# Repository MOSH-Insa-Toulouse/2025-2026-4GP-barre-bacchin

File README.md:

# Partie I : Contexte 

Le but de ce projet est de réaliser un capteur de flexion lowtech à base de crayon à papier et d'une feuille de papier.  
L'origine de ce projet vient d'un article publié en 2014 dans Nature par _Lin, CW, Zhao, Z., Kim, J. et al._ nommé "**Pencil Drawn Strain Gauges and Chemiresistors on Paper "**.  
Le capteur est dessiné par dépot de graphite sur une feuille à l'aide d'un crayon de papier. Ce dépot est un système granulaire dont la conductance dépend de la distance inter-grain. Plus la distance inter-grain diminue, plus la conductance augmente. C'est exactement ce qu'il se passe lorsque la feuille est placé en compression. De ce fait, on peut théoriquement déduire l'angle de flexion de la feuille en fonction de la résistance du capteur.  
  
Notre travail consiste a réaliser le capteur, le circuit électronique de lecture et de le tester afin de le comparer à des capteurs commerciaux. 

## Partie I.1 : Liste des Livrables

1. Un shield PCB adapté pour une Arduino UNO permettant de faire la mesure de résistance du capteur graphite, celle du capteur commercial et de connecter un module Bluetooth pour envoyer les résulats sur une application.
2. Une application Android (sous MIT App Inventor) permettant de voir la valeur de la résistance mesuré et la variation relative de résistance.
3. Le code Arduino qui gère la mesure de flexion et le module bluetooth
4. Le protocole de mesure du banc de test
5. La datasheet du capteur graphite

## Partie I.2 : Liste du matériel utilisé

1. Capteur en graphite 
   - Feuille de papier d'épaisseur 0.35mm
   - Différents crayons à papier (B, 3B et 6B)
2. Arduino et modules
   - Carte Arduino UNO + câble USB
   - Module Bluetooth HC-05
   - Flex Sensor + résistance de 47 kΩ
3. Circuit amplificateur
   - Amplificateur opérationnel LTC1050
   - Condensateurs : 2* 100 nF + 1* 1 µF
   - Résistances :  1* 1kΩ + 1* 10kΩ + 2* 100kΩ
   - Potentiomètre digital MCP 41010
4. Matériel pour réaliser le PCB
   - Plaque d'époxy recouverte d'une couche de cuivre et de résine photosensible
   - Matériel de développement : Machine UV + révélateur + perclorure de fer
   - Machine à perforer
   - Fer à souder + étain
   - Pin headers
5. Banc de test
   - Banc de test creux avec différents rayons de courbures connus.

# Partie II : Réalisation théorique

## Partie II.1 : Conception du circuit amplificateur
La résistance du capteur est énorme, de l'ordre du Mega-Ohm, ainsi le courant obtenu en sortie est très faible. Il nous faut donc amplifier le signal afin de l'exploiter.  

Pour ce faire nous avons réaliser un circuit amplificateur transimpédance que nous avons simulé sur LTSpice visible en figure II.1
<p align="center">
  <br>
  <em>Figure II.1 – Schéma LTSpice du capteur et du circuit amplificateur</em>
</p>

Sur le logiciel de simulation, nous avons modélisé l’alimentation de l’Arduino en 5 V, alimentation qui fournit également l’énergie nécessaire au capteur et à l’amplificateur opérationnel (AOP).
Le capteur a ensuite été représenté à l’aide d’un générateur de pulses, ce qui permet de simuler son comportement dynamique.
Afin de reproduire des conditions réelles, une source de bruit a été ajoutée au montage. 

Le circuit amplificateur est constitué de trois filtres passe-bas, chacun ayant un rôle bien précis dans l’élimination des bruits indésirables.

   - Filtre passe-bas 16 Hz (en entrée)

Ce filtre permet de supprimer les bruits parasites provenant de vibrations mécaniques ou de tremblements.

$$ Fc_{1}  = \frac{1}{2\pi * C1 * R1 } = \frac{1}{2\pi * 100n * 100k}  ≃ 16 Hz$$

   - Filtre passe-bas 1.6 Hz (réduction du bruit 50 Hz)

Ce filtre atténue les résidus issus du bruit secteur 50 Hz.

$$ Fc_{2}  = \frac{1}{2\pi * C2 * R4 } = \frac{1}{2\pi * 1µm * 100k}  ≃ 1.6 Hz $$

   - Filtre passe-bas 1.6 kHz (en sortie de l’AOP)

Ce filtre élimine les bruits haute fréquence générés par l’électronique (AOP, câblage, parasites HF).

$$ Fc_{3}  = \frac{1}{2\pi * C3 * R5 } = \frac{1}{2\pi *100n * 1k}  ≃ 1.6 KHz $$

Plusieurs simulations ont été effectuées afin de vérifier :
- L'amplication du signal fourni par le capteur
- La filtration du bruit 

À partir du montage, il est également possible de déterminer la relation mathématique reliant la résistance du capteur à sa tension de sortie : 
<p align="center">
   <br>
  <em> (Eq.1) </em>
</p>

## Partie II.2 : Design du PCB sous KiCad

Une fois la forme du circuit fixé et tous les modules connectés à l'Arduino chosis, nous avons pu concevoir la shield.  
Pour ce faire, nous utilisons le logiciel KiCad. 
Comme tous les composants n'étaient pas présent dans la bibliothèque de composant de KiCad, nous avons dû réalisé les schématiques et les empreintes du flex sensor, du capteur graphite, du module bluetooth et du potentiomètre digital.   
Voilà le schématique complet de notre shield :   

<p align="center">
  <br>
  <em>Figure II.2 – Schématique kicad du projet</em>
</p>

Concernant les empreintes, nous n'allons pas souder les composants onéreux directement. Ainsi pour le flex sensor et le module bluetooth nous avons prévu des pins dans lesquels nous brancherons les modules. Pour l'AOP et le potentiomètre nous allons souder des support DIP8.  
Ainsi notre empreinte ressemble à cela :  
<p align="center">
  <br>
  <em>Figure II.3 – Empreinte du projet</em>
</p>

Enfin la modélisation 3D donne :  

<p align="center">
 <br>
  <em>Figure II.4 – Modélisation 3D du projet</em>
</p>

# Partie III : Fabrication du PCB

Une fois le PCB conçu, vérifié et corrigé sous KiCad, nous pouvons passer à sa fabrication. Pour cela, le circuit est exporté depuis KiCad sous la forme d’un fichier typon, qui servira de base pour la gravure du circuit imprimé.

<p align="center">
 <br>
  <em>Figure III.1 – Fichier typon </em>
</p>

## Partie III.1 : Développement

Le fichier typon est imprimé sur une feuille transparente afin de créer un masque. Ce masque est ensuite positionné sur une plaque d’époxy recouverte de cuivre et d’une résine photosensible.La plaque est exposée aux rayons UV, ce qui permet de transférer le motif des pistes du typon sur la résine. Après exposition, la plaque est plongée dans un révélateur afin d’éliminer la résine photosensible des zones exposées. Elle est ensuite immergée dans un bain de perchlorure de fer, qui dissout le cuivre non protégé et fait apparaître les pistes du circuit.

Une fois cette étape terminée, les pistes sont vérifiées à l’aide d’un multimètre afin de détecter d’éventuelles coupures ou courts-circuits. Certaines pistes imparfaitement révélées ont été corrigées manuellement à l’aide d’un cutter.

## Partie III.2 : Création du PCB

Après la gravure, les trous nécessaires à l’implantation des composants sont percés à l’aide de deux forets de diamètres différents : 0,8 mm et 1 mm, en fonction des composants. Les composants électroniques sont ensuite soudés sur la carte. Un via a également été réalisé en soudant un fil reliant une piste spécifique à la masse, comme indiqué sur le typon.
<p align="center">
  
  <br>
  <em>Figure III.2 – Soudure du PCB avec un via </em>
</p>

## Partie III.3 : Tests

Enfin, des tests ont été réalisés pour vérifier le bon fonctionnement du circuit. Nous avons notamment vérifié que l’amplificateur amplifiait correctement la tension de sortie du capteur.

# Partie IV : Code Arduino

Pour créer le code final Arduino chargé de gérer les différents composants ; le potentiomètre digital, le module Bluetooth, le flex sensor et l’AOP. Nous avons d’abord testé ,indépendamment, l’ensemble des éléments du circuit final sur une breadboard 
puis, chaque code a été adapté pour être cohérent avec notre projet.
Enfin nous avons regroupé ces codes pour obtenir un code global qui contrôle tous les modules ensemble.

## Partie IV.1 : Code du potentiomètre digital

Le potentiomètre digital est contrôlé en lui envoyant un indice compris entre 0 et 255, lequel détermine une valeur de résistance.
Après caractérisation expérimentale, nous avons observé que le potentiomètre suit la loi :

$$ R=58+indice×37 \quad (Ω)$$

Une fonction de centrage est exécutée dans la void setup() du programme.
Son objectif est de centrer le signal de sortie autour de 2,5 V en ajustant la résistance du potentiomètre digital.

Une boucle for fait varier l’indice de 0 à 255.
Pour chaque valeur, nous envoyons l’indice au potentiomètre et vérifions si la tension de sortie se situe autour de 2,5 V ± 0,4 V.
Si cette condition est remplie, la boucle est interrompue.
Si elle ne l’est jamais, la boucle se termine naturellement et nous conservons l’indice pour lequel la tension était la plus proche de 2,5 V.

À partir de cet indice, nous déduisons la résistance du potentiomètre $$𝑅_{2}$$ grâce à la loi caractérisée puis, grâce à l’équation 1, nous retrouvons la résistance initiale du capteur avant déformation, notée $$𝑅_{0}$$

## Partie IV.2 : Code pour le flex sensor

Nous utilisons une fonction mesure_flex() qui renvoie la variation relative de résistance du flex sensor.

Nous mesurons d’abord la tension aux bornes du flex, notée $$𝑉_{flex}$$.
La résistance du flex sensor est obtenue via :

$$ R_{flex} = R_{div}* (\frac{Vcc}{V_{flex}} -1)$$

En connaissant la résistance du flex à plat $$𝑅_{flat}$$ et la resistance du pont diviseur $$R_{div} = 47 kΩ$$.

Nous pouvons aussi calculer la variation relative de la resistance du flex sensor : $$\frac{R_{flex} - R_{flat}}{ R_{flat}}$$
	​
## Partie IV.3 : Application MIT Bluetooth

Les informations suivantes sont envoyées à l’application Bluetooth, séparées par des points :

- la variation relative du capteur
- la variation relative du flex sensor
- la résistance du capteur avant déformation ( $$R_{0}$$)
- la résistance du potentiomètre digital ( $$R_{2}$$)

Ces données sont envoyées depuis le programme principal Arduino.

Voici le code de notre application MIT :
<p align="center">
 <br>
  <em>Figure IV.1 – Code de l'application MIT</em>
</p>

L’application MIT reçoit en boucle les informations envoyées, les place dans une liste, puis exécute les opérations suivantes uniquement lorsque la liste contient 4 éléments :  
	- Les résistances $$R_{0}$$ et $$R_{2}$$ sont affichées dans des zones de texte   
	- les variations relatives sont ajoutées aux deux graphes : un graphique pour le flex sensor et un graphique pour le capteur.

L’interface de l’application est présentée ci-dessous :
<p align="center">
  
  <br>
  <em>Figure IV.2 – Face avant de l'application MIT, à gauche dans la phase de design, à droite en utilisation </em>
</p>

# Partie V : Banc de test et caractérisation

Le circuit et le code étant fonctionnel, nous nous sommes lancé dans la caractérisation du capteur. Pour cela nous utilisons un banc de test, présenté en figure V.1, dont les dimensions sont connues. Grâce au programme de centrage, on obtient une tension centré autour de 2.5V et on rappelle que la résistance du capteur est donnée par la formule : 
<p align="center">
   <br>
  <em> (Eq.1) La resistance 2 étant celle du potentiomètre digital </em>
</p>
Le banc de test a des rayons de courbures allant de 1cm à 2,5cm par incrément de 0,25cm. Pour réaliser la mesure on étale le capteur sur le banc de test en le fixant de sorte à ce qu'il épouse la forme. Par cette technique la déformation appliquée est connue et contrôlée, nous permettant de caractériser de manière fiable le capteur.  
Les variables d'intérêts sont la variation relative de résistance et la déformation, elles sont définies comme : 
<p align="center"> 
  <br>
  <em>(Eq.2) Ici R0 correspond à la résistance du capteur lorsqu'il est plat (flat resistance) </em>
</p>

Avec tout cela nous avons pu obtenir les courbes caractéristiques de notre capteur en fonction de différents crayons à papier utilisé. Pour cela deux méthodes ont été employées :<br>  
- Méthode 1 : la résistance R0 n'est redéterminée qu'au début des mesures   <br>   
- Méthode 2 : la résistance R0 est redéterminée entre chaque mesure  <br>   
Ces deux méthodes sont nécessaires car le capteur est très sensible à la perte de matière dû aux utilisations, ainsi la resistance R0 peut beaucoup varier d'une mesure à une autre. Cependant, dans une application réelle, il n'est pas forcément possible de revenir à l'état plat entre chaque mesure ainsi la méthode 1 est importante.  <br>
<br>
<p align="center">
  
  <br>
  <em>Figure V.1 : Banc de test utilisé </em>
</p>

Les différentes courbes obtenues sont présentés ci-dessous, le coefficient de proportionnalité sur les courbes linéaires correspond à la sensibilité du capteur. La déformation en compression n'a été faite qu'avec le crayon 6B car ce test est plus coûteux en matière pour le capteur. Ainsi, sur les crayons moins gras, l'augmentation de résistance dû à la perte de matière prédominait devant la chute dû à la compression.

**Crayon 6B** 
<p align="center"> 
  <br>
  <em>Figure V.2 : Courbe charactéristique du capteur avec le crayon 6B en tension </em>
</p>
<p align="center"> 
  <br>
  <em>Figure V.3 : Courbe charactéristique du capteur avec le crayon 6B en compression </em>
</p>

**Crayon 3B**
<p align="center"> 
  <br>
  <em>Figure V.4 : Courbe charactéristique du capteur avec le crayon 3B en tension </em>
</p>

**Crayon B** 
<p align="center"> 
  <br>
  <em>Figure V.5 : Courbe charactéristique du capteur avec le crayon B en tension </em>
</p>

**Capteur commercial**
<p align="center"> 
  <br>
  <em>Figure V.6 : Courbe charactéristique du capteur commercial en tension </em>
</p>

Il est clair que le capteur que le capteur se détériore au fil des utilisations car la méthode 1 et la méthode 2 ne donnet pas les mêmes résultats.  
On remarque que la sensibilité est plus forte pour les crayons moins gras, cependant la resistance étant beaucoup plus grande le signal et les mesures obtenues sont beaucoup plus irrégulières et le capteur moins durable. En effet, le capteur perd trop de matière trop vite pour être utilisé de manière répétée.  La linéarité du capteur se voit particulièrement sur le crayon 6B qui a une courbe de tendance proche des données mesurées.  
Par ailleurs, sur le crayon 3B avec la méthode 2, on observe clairement un comportement exponentiel, se rapprochant de la théorie des systèmes granulaires.  
En comparaison avec le capteur commercial, présenté en figure V.6, notre capteur a une piètre sensibilité et surtout subit des déformations irréversibles modifiant sa résistance à plat contrairement au capteur commercial.

# Partie VI : Conclusion
L’objectif de ce projet était de déterminer si un capteur en graphite pouvait être industrialisé. Pour y parvenir, nous avons réalisé l’ensemble du processus de développement : conception et fabrication du capteur, création du circuit amplificateur, design et production du PCB, ainsi que le développement logiciel nécessaire au traitement du signal. L’ensemble de cette chaîne nous a permis d’obtenir un capteur fonctionnel et une acquisition des données opérationnelle. Un banc de test a également été développé afin d’évaluer le comportement du capteur avec différents crayons et sous des déformations mécaniques contrôlées.

Les résultats obtenus montrent que la sensibilité du capteur varie fortement, généralement entre 30 et 100 selon le type de crayon utilisé. Cette variabilité importante, ainsi que les niveaux de sensibilité obtenus, restent loin des performances attendues pour une jauge de contrainte industrielle. Malgré cela, notre capteur présente plusieurs qualités : il est capable de mesurer aussi bien la traction que la compression, il est extrêmement économique, rapide à produire, accessible à tous et facilement remplaçable.

Cependant, plusieurs limitations majeures compromettent toute industrialisation dans l’état actuel. Les points de contact sont instables et modifient la mesure au cours du temps. Le capteur se déforme rapidement, parfois dès les premières utilisations, et sa durée de vie ne dépasse pas une dizaine de mesures fiables. De plus, la perte progressive du graphite altère inévitablement la répétabilité et la précision des résultats.

Ainsi, dans sa forme actuelle, ce capteur ne peut pas être considéré comme industrialisable. Toutefois, certaines améliorations pourraient significativement augmenter sa fiabilité, par exemple l’utilisation d’électrodes fixes, la plastification du capteur afin de stabiliser le graphite et d’éviter la dégradation du papier. Si l’on considère que la majorité des dérives provient de la perte de matière graphite plutôt que d’une modification durable de la structure conductrice, alors ces améliorations pourraient rendre le capteur plus stable et durable.

<p align="center"> 
  <br>
  <em>Figure VI : Tableau comparatif du capteur graphite et du capteur industriel </em>
</p>

# Contacts

Voici nos contacts si vous souhaitez des informations complémentaires

Bacchin Lisa : bacchin@insa-toulouse.fr
Barre Ronan : barr@insa-toulouse.fr

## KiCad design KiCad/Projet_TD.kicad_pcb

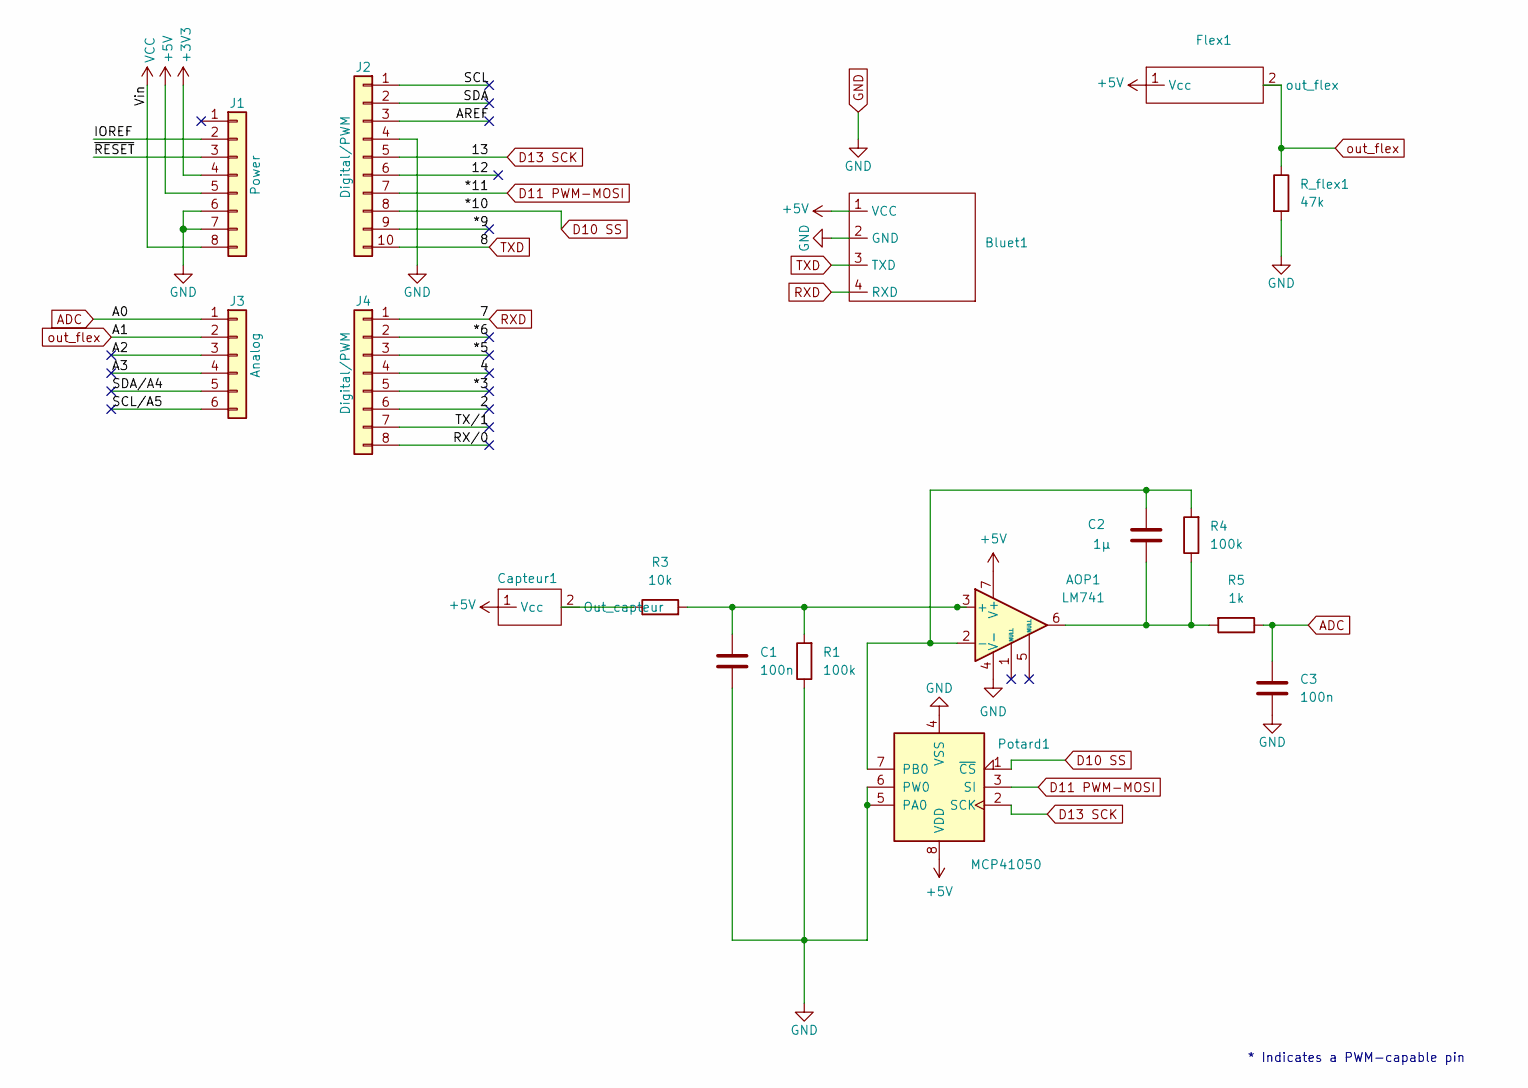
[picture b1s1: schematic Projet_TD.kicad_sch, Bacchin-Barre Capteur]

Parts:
AOP1: LM741; AOP_si_besoin
Bluet1: Bluetooth-HC05
C1, C3: 100n; C_Axial_L3.8mm_D2.6mm_P10.00mm_Horizontal
C2: 1µ; C_Rect_L7.0mm_W6.0mm_P5.00mm
Capteur1: Capteur
Flex1: flex_sensor
J1: Power; PinSocket_1x08_P2.54mm_Vertical
J2: Digital/PWM; PinSocket_1x10_P2.54mm_Vertical
J3: Analog; PinSocket_1x06_P2.54mm_Vertical
J4: Digital/PWM; PinSocket_1x08_P2.54mm_Vertical
Potard1: MCP41050; DIP-8_W7.62mm
R1, R4: 100k; R_Axial_DIN0207_L6.3mm_D2.5mm_P7.62mm_Horizontal
R3: 10k; R_Axial_DIN0207_L6.3mm_D2.5mm_P7.62mm_Horizontal
R5: 1k; R_Axial_DIN0207_L6.3mm_D2.5mm_P7.62mm_Horizontal
R_flex1: 47k; R_Axial_DIN0207_L6.3mm_D2.5mm_P7.62mm_Horizontal

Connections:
+3V3: J1.4
+5V: AOP1.7 (V+), Bluet1.1 (VCC), Capteur1.1 (Vcc), Flex1.1 (Vcc), J1.5, Potard1.8 (VDD)
/2: J4.6
/4: J4.4
/12: J2.6
/*3: J4.5
/*5: J4.3
/*6: J4.2
/*9: J2.9
/A2: J3.3
/A3: J3.4
/AREF: J2.3
/IOREF: J1.2
/RX/0: J4.8
/SCL: J2.1
/SCL/A5: J3.6
/SDA: J2.2
/SDA/A4: J3.5
/TX/1: J4.7
/~RESET: J1.3
ADC: C3.1, J3.1, R5.1
D10 SS: J2.8, Potard1.1 (~CS)
D11 PWM-MOSI: J2.7, Potard1.3 (SI)
D13 SCK: J2.5, Potard1.2 (SCK)
GND: AOP1.4 (V-), Bluet1.2 (GND), C1.2, C3.2, J1.6, J1.7, J2.4, Potard1.4 (VSS), Potard1.5 (PA0), Potard1.6 (PW0), R1.1, R_flex1.2
unnamed: AOP1.3 (+), C1.1, R1.2, R3.2
unnamed: AOP1.2 (-), C2.1, Potard1.7 (PB0), R4.2
unnamed: AOP1.6, C2.2, R4.1, R5.2
unnamed: Capteur1.2 (Out_capteur), R3.1
RXD: Bluet1.4 (RXD), J4.1
TXD: Bluet1.3 (TXD), J2.10
VCC: J1.8
out_flex: Flex1.2 (out_flex), J3.2, R_flex1.1

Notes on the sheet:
* Indicates a PWM-capable pin

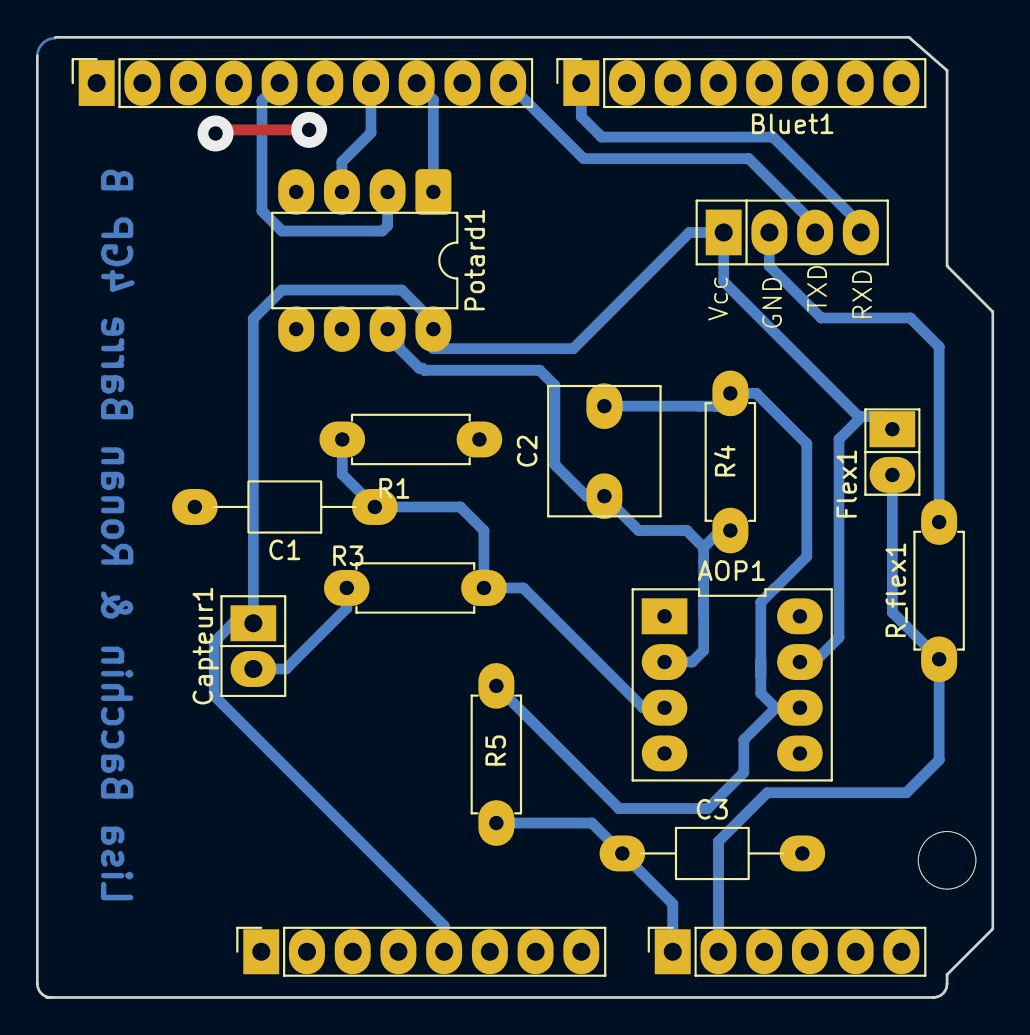
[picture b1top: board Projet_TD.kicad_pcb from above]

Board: 2 copper layers, 53.1 x 53.3 mm, 18 parts (0 on the bottom side), 13 nets.

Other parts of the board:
MH4: MountingHole_3.2mm

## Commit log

2026-02-10 ijoerdv rùgr$
2026-02-10 Ma branche kicad
2026-02-21 Add .gitignore for LaTeX auxiliary files
2026-03-22 Add section 'Partie I : Contexte du sujet' to README
2026-03-22 add part to readme
2026-03-22 Add part title
2026-04-11 Update README.md
    Materiel utilisé
2026-04-11 Update README.md
    Partie fabrication du pcb
2026-04-14 Update README.md
    Photos
2026-04-14 Update README.md
    photo
2026-04-14 Add files via upload
    nouvelle arborescence
2026-04-14 Update README.md
    Ajout des légendes des photos
2026-04-15 added the part IV text
    Added detailed characterization of the sensor using a test bench, including methods and results for different pencil types.
2026-04-15 finalize parte IV
2026-04-15 prtout protu
2026-04-15 Update README.md
    Joyeux anniversaire
2026-04-15 ALED
2026-04-16 FOTOLMIT
2026-04-16 Update README.md
    kzijoeesokdos
    rioeràoi
2026-04-16 Update README.md
    Corrections de petits problemes
2026-04-16 Readme_modif
    joyeux anniv lolo + correction et clarification du readme
2026-04-16 add all files
2026-04-20 Update README.md
    Ajout typon
